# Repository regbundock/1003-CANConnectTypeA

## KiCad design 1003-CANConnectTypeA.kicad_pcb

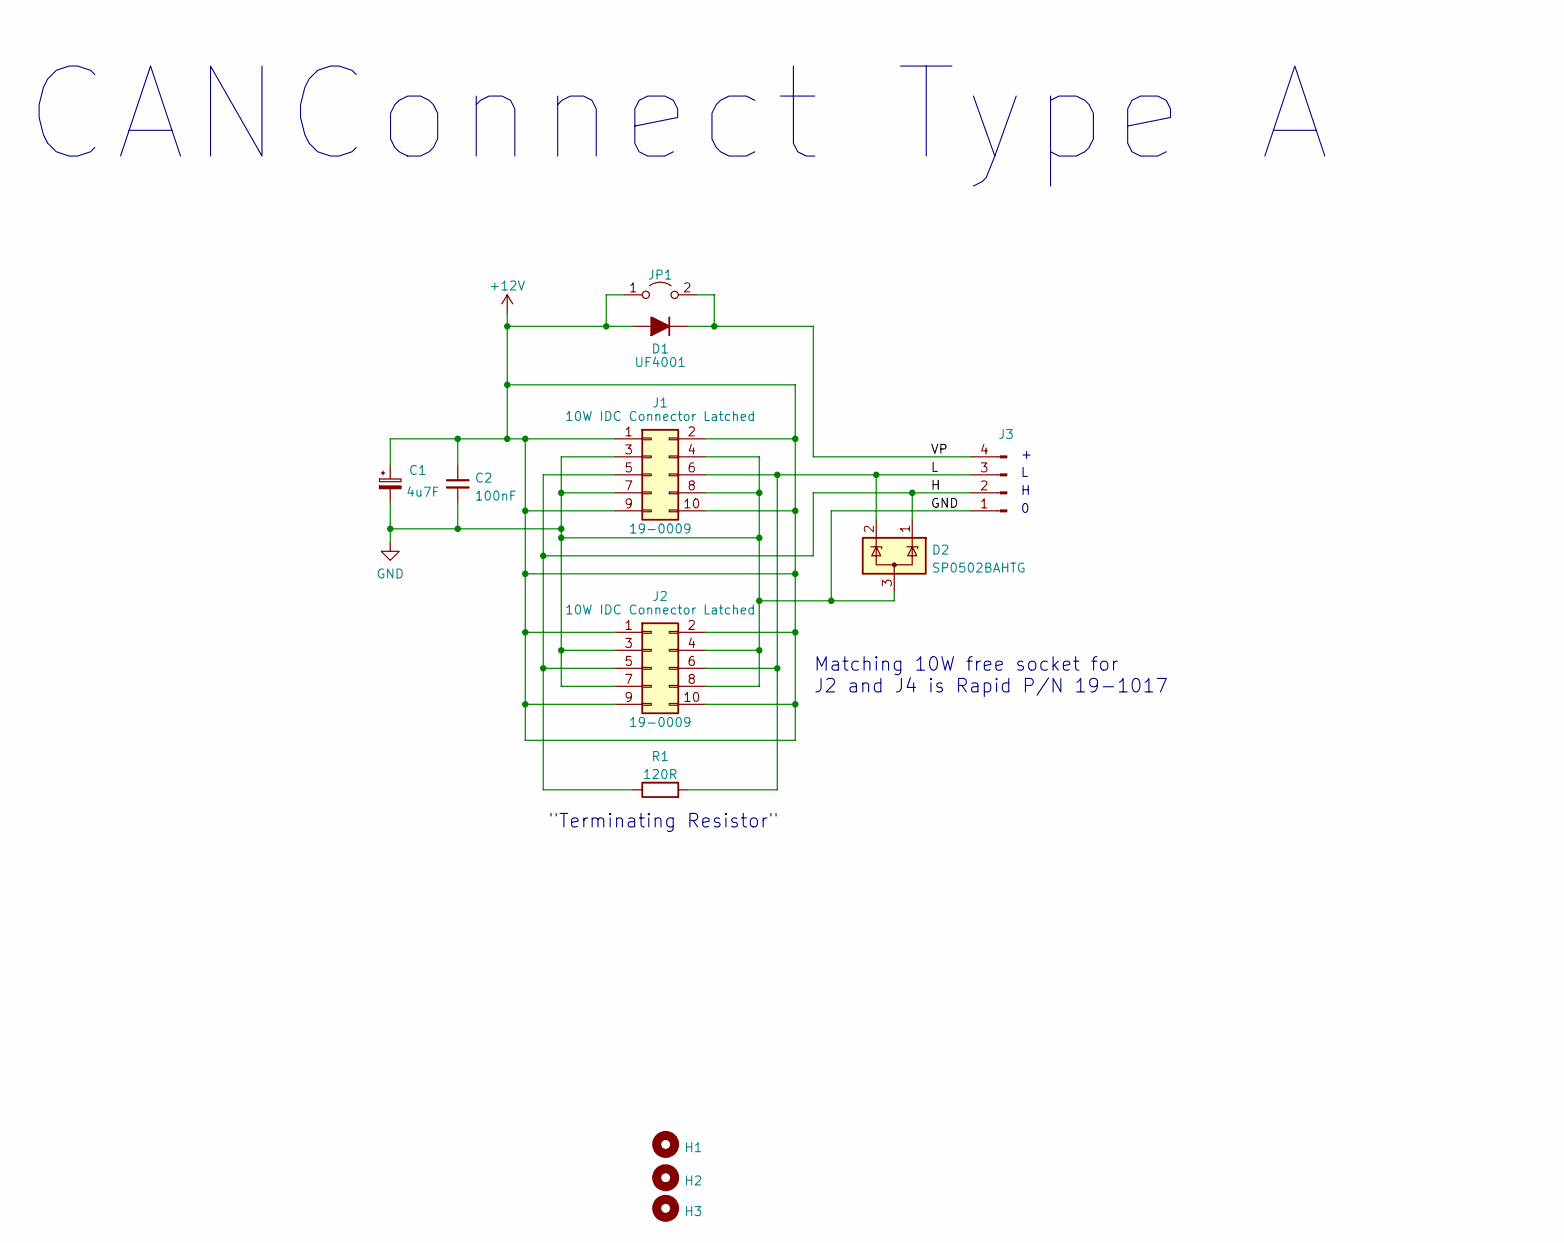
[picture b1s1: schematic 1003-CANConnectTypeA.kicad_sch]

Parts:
C1: 4u7F; CP_Radial_Tantal_D4.5mm_P5.00mm
C2: 100nF; C_Disc_D5.0mm_W2.5mm_P5.00mm
D1: UF4001; D_DO-41_SOD81_P10.16mm_Horizontal
D2: SP0502BAHTG; SOT-23
H1, H2, H3: MountingHole; MountingHole_3.2mm_M3_DIN965_Pad_TopBottom
J1, J2: 10W IDC Connector Latched; IDC-Header_2x05_P2.54mm_Latch_Vertical; Part No. 19-0009
J3: Conn_01x04_Male; Camdenboss_3pt5mm_pitch_PCB_horizontal_4Way
JP1: Jumper_2_Open; PinHeader_1x02_P2.54mm_Vertical
R1: 120R; R_Axial_DIN0207_L6.3mm_D2.5mm_P10.16mm_Horizontal

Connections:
+12V: C1.1, C2.1, D1.2 (A), J1.1, J1.2, J1.9, J1.10, J2.1, J2.2, J2.9, J2.10, JP1.1 (A)
/H: D2.1 (K), J1.5, J2.5, J3.2, R1.1
/L: D2.2 (K), J1.6, J2.6, J3.3, R1.2
/VP: D1.1 (K), J3.4, JP1.2 (B)
GND: C1.2, C2.2, D2.3 (A), J1.3, J1.4, J1.7, J1.8, J2.3, J2.4, J2.7, J2.8, J3.1

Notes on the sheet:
"Terminating Resistor"
CANConnect Type A
Matching 10W free socket for J2 and J4 is Rapid P/N 19-1017

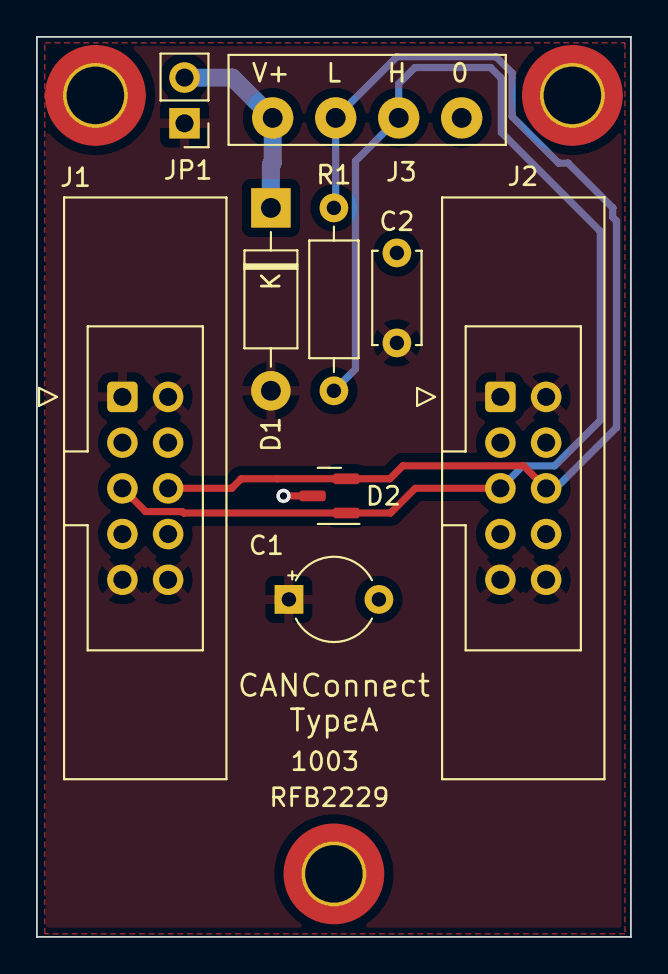
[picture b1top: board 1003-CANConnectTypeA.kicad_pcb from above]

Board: 2 copper layers, 33.0 x 50.0 mm, 12 parts (0 on the bottom side), 5 nets.
